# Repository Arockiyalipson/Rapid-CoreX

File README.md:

# Rapid_CoreX 

## Introduction

Rapid-CoreX is a versatile Rapid control prototyping (RCP) designed for embedded systems development, testing, and integration. It supports essential communication protocols and allows for easy connection and testing of various sensors or devices using MATLAB software. Rapid-CoreX is particularly useful for testing external parameters of Battery Management Systems (BMS), motor controllers, and other connected devices.

## Tools Used

- **KiCad:** Used for schematic capture and PCB layout design.
- **STM32CubeMX:** Used for setting up the pin map for the design

## Design Structure

```bash
Rapid-CoreX
        │
        ├───Design
        │
        ├───Images
        │
        ├───Library
        │   ├───Symbols
        │   ├───Footprint
        │   └───3D_Images
        ├───Manufacturing_files
        │   ├───Bom file
        │   ├───Component position files
        │   ├───Drill files
        │   ├───Gerber files
        │   └───Reference_material
        └───Reference
```

## Features

### Communication Protocols

Rapid-CoreX includes the following communication protocols for sensor connection, data collection, and interconnection:

#### Basic Protocols

- **SPI**: Serial Peripheral Interface for high-speed communication.
- **I2C**: Inter-Integrated Circuit for connecting multiple sensors.
- **UART**: Universal Asynchronous Receiver-Transmitter for serial communication.

#### Debugging

- **SWD**: Serial Wire Debug for in-circuit debugging and programming.

#### Data Collection and Interconnection Protocols

- **CAN**: Controller Area Network for real-time data exchange in automotive and industrial applications.
- **RS-485**: A robust standard for long-distance communication.
- **LIN**: Local Interconnect Network, used in automotive networks for communication between components.

All data collection protocols are isolated to ensure better protection and signal integrity.

### Communication Ports

Rapid-CoreX is equipped with various ports to facilitate connectivity:

- **2 x CAN** ports for network communication.
- **2 x RS-485** ports (USART) for long-distance and robust communication.
- **2 x LIN** ports for automotive applications.
- **1 x External SPI** ports for additional SPI device connectivity.

### GPIO Features

- **User LED**: Available for user-defined visual indication.

## Applications

Rapid-CoreX is ideal for:

- Testing external parameters of Battery Management Systems (BMS).
- Testing motor controllers.
- Integrating and testing various sensors.
- Development and testing of embedded systems that require robust and isolated communication.

## Getting Started

### Prerequisites

To use Rapid-CoreX, ensure you have the following:

- MATLAB software for interfacing and testing.
- Necessary drivers and libraries for STM32 Cortex-M4.

### Setup

1. Connect your sensors or sister devices to the appropriate communication ports on Rapid-CoreX.
2. Use MATLAB to interface with Rapid-CoreX for data collection and testing.
3. For debugging, connect through the SWD interface.

### Usage

1. Power on the Rapid-CoreX and ensure all connections are secure.
2. Implement a MATLAB Developed Algorithm in the board
3. Start collecting Data and Analyze it 

## Contact

For more information, please contact [Arockiya Lipson](https://www.linkedin.com/in/arockiya-lipson-458b12214).

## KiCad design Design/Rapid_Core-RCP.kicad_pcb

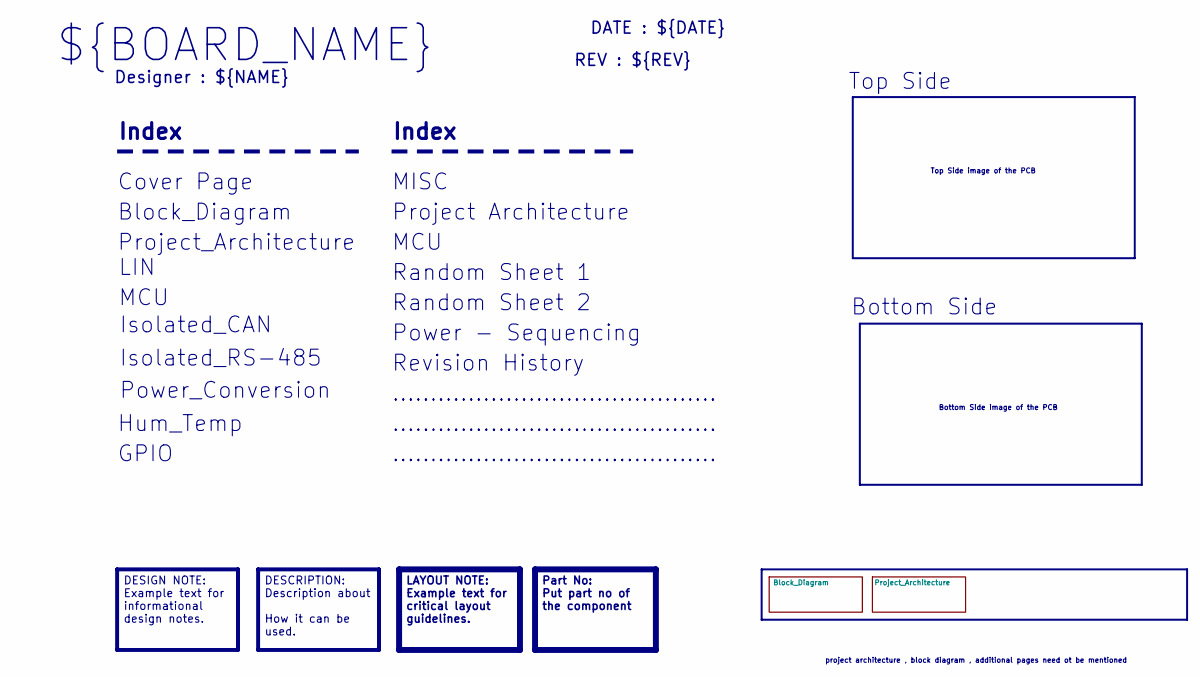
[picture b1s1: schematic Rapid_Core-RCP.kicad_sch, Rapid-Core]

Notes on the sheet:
DESCRIPTION: Description about How it can be used.
Part No: Put part no of the component
DESIGN NOTE: Example text for informational design notes.
LAYOUT NOTE: Example text for critical layout guidelines.
...........................................
Top Side image of the PCB
MISC
Power_Conversion
Designer : ${NAME}
Random Sheet 1
Revision History
Hum_Temp
project architecture , block diagram , additional pages need ot be mentioned
Cover Page
Power - Sequencing
Bottom Side image of the PCB
DATE : ${DATE}
Project_Architecture
Top Side
Isolated_RS-485
${BOARD_NAME}
Index
Bottom Side
REV : ${REV}
GPIO
Isolated_CAN
Random Sheet 2
MCU
Project Architecture
LIN
Block_Diagram

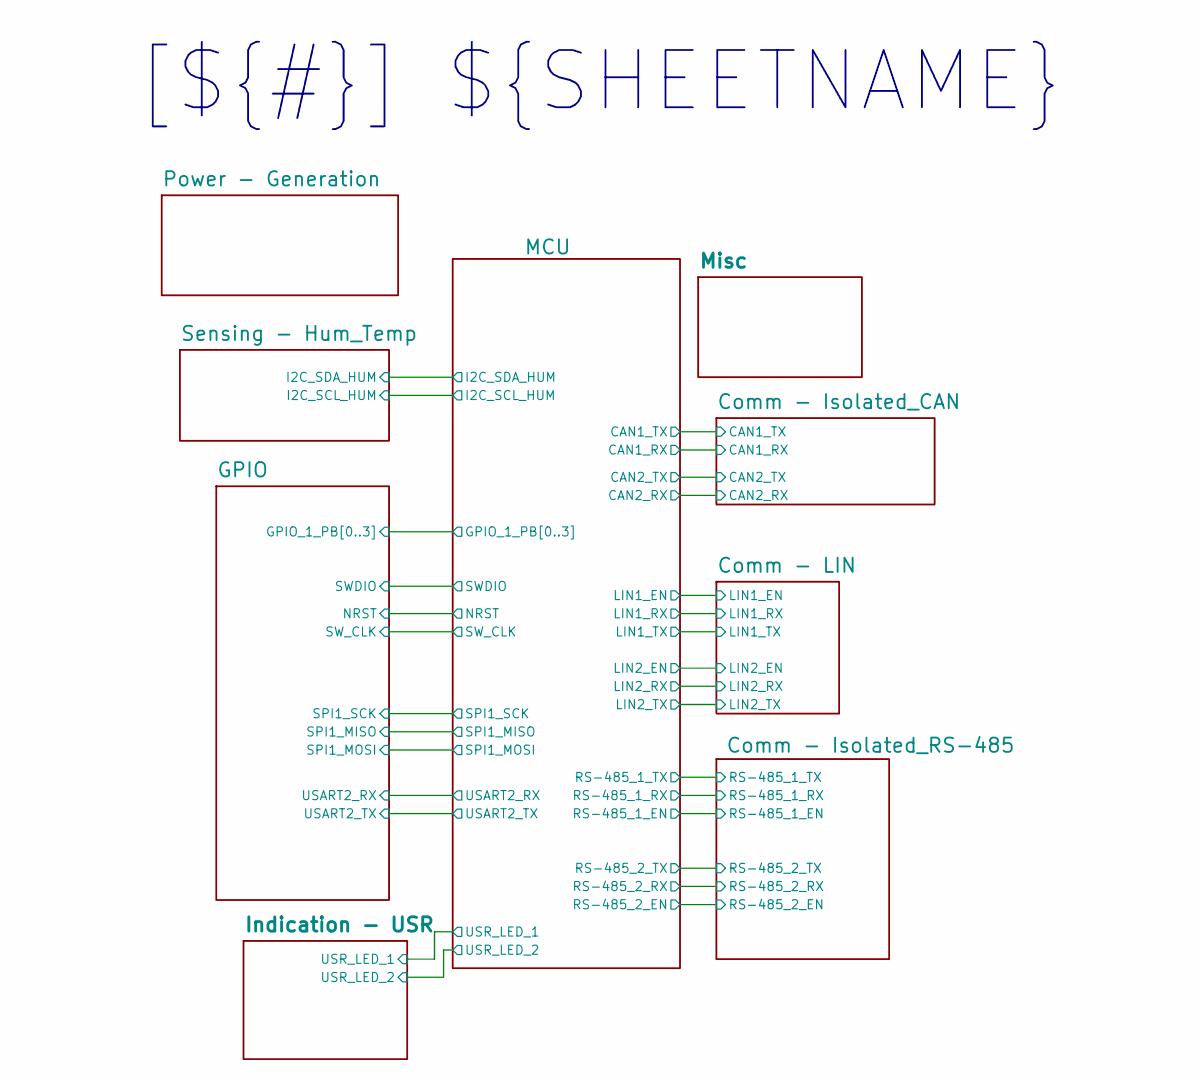
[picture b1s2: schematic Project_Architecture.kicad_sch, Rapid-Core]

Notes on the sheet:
[${#}] ${SHEETNAME}

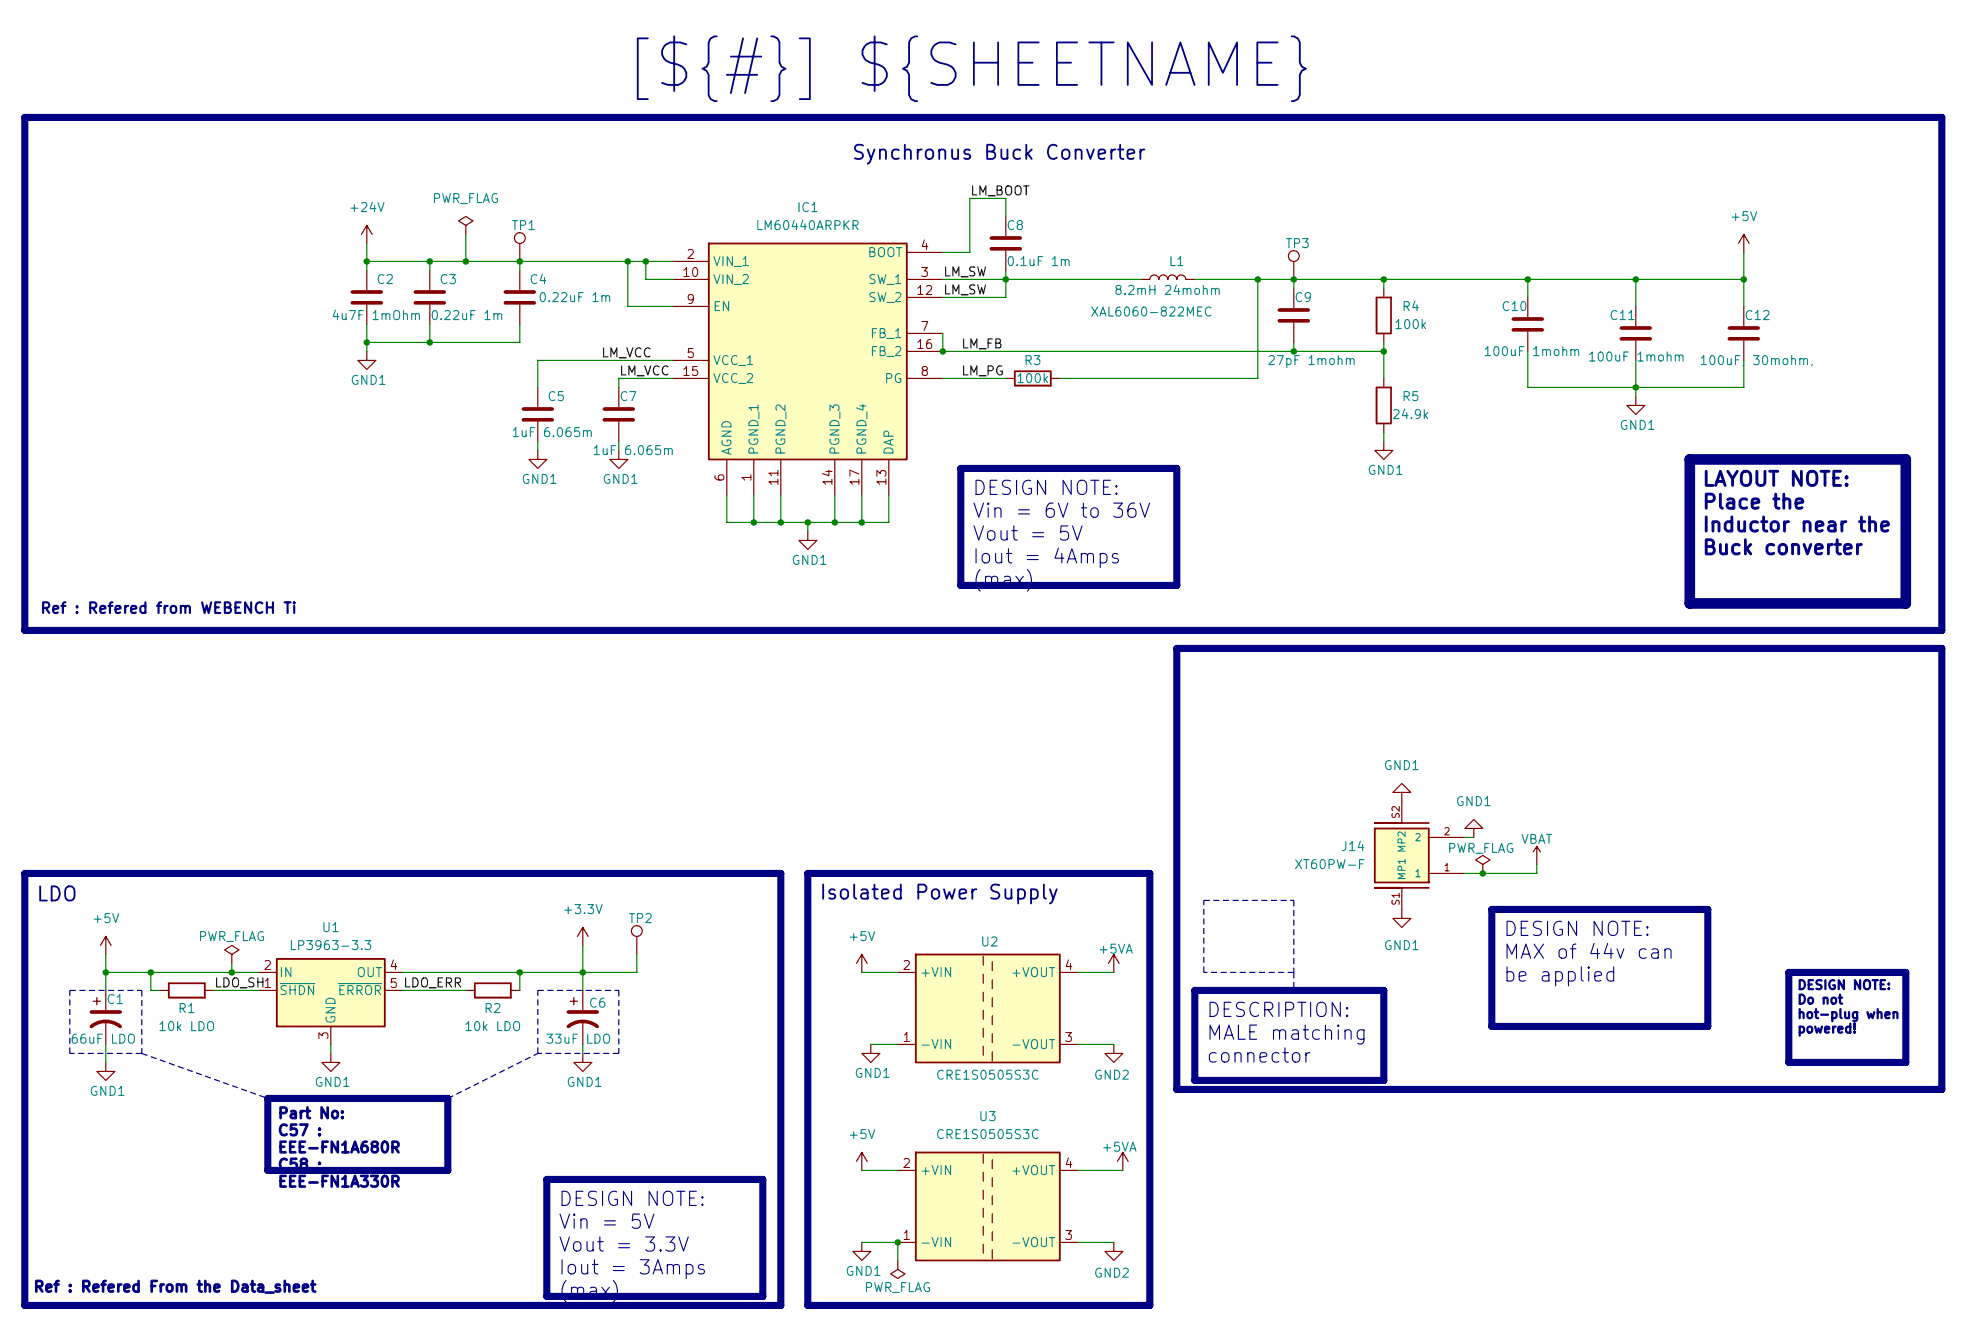
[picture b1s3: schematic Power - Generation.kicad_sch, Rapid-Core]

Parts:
C1: 66uF LDO; CP_Elec_5x5.8
C2: 4u7F 1mOhm; C_0805_2012Metric_Pad1.18x1.45mm_HandSolder
C3, C4: 0.22uF 1m; C_0603_1608Metric_Pad1.08x0.95mm_HandSolder
C5, C7: 1uF 6.065m; C_0603_1608Metric_Pad1.08x0.95mm_HandSolder
C6: 33uF LDO; CP_Elec_4x5.8
C8: 0.1uF 1m; C_0603_1608Metric_Pad1.08x0.95mm_HandSolder
C9: 27pF 1mohm; C_0805_2012Metric_Pad1.18x1.45mm_HandSolder
C10, C11: 100uF 1mohm; C_0805_2012Metric_Pad1.18x1.45mm_HandSolder
C12: 100uF, 30mohm,; C_0805_2012Metric_Pad1.18x1.45mm_HandSolder
IC1: LM60440ARPKR; LM60440AQRPKRQ1; Mouser Part Number 595-LM60440ARPKR
J14: XT60PW-F; AMASS_XT60PW-F
L1: 8.2mH 24mohm; L_Coilcraft_XAL6060-XXX; MANUFACTURER PART NO XAL6060-822MEC
R1, R2: 10k LDO; R_0805_2012Metric_Pad1.20x1.40mm_HandSolder
R3, R4: 100k; R_0805_2012Metric_Pad1.20x1.40mm_HandSolder
R5: 24.9k; R_0805_2012Metric_Pad1.20x1.40mm_HandSolder
TP1, TP2, TP3: TestPoint; TestPoint_Pad_D1.0mm
U1: LP3963-3.3; TO-263-5_TabPin3
U2, U3: CRE1S0505S3C; Converter_DCDC_Murata_CRE1xxxxxx3C_THT

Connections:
+3.3V: C6.1, R2.2, TP2.1, U1.4 (OUT); also elsewhere on the board
+5V: C1.1, C9.1, C10.1, C11.1, C12.1, L1.2, R1.1, R3.2, R4.2, TP3.1, U1.2 (IN), U2.2 (+VIN), U3.2 (+VIN); also elsewhere on the board
+5VA: U2.4 (+VOUT), U3.4 (+VOUT); also elsewhere on the board
+24V: C2.1, C3.1, C4.1, IC1.2 (VIN_1), IC1.9 (EN), IC1.10 (VIN_2), TP1.1
/Project_Architecture/Power - Generation/LDO_ERR: R2.1, U1.5 (~ERROR)
/Project_Architecture/Power - Generation/LDO_SH: R1.2, U1.1 (~SHDN)
/Project_Architecture/Power - Generation/LM_BOOT: C8.1, IC1.4 (BOOT)
/Project_Architecture/Power - Generation/LM_FB: C9.2, IC1.7 (FB_1), IC1.16 (FB_2), R4.1, R5.2
/Project_Architecture/Power - Generation/LM_PG: IC1.8 (PG), R3.1
/Project_Architecture/Power - Generation/LM_SW: C8.2, IC1.3 (SW_1), IC1.12 (SW_2), L1.1
/Project_Architecture/Power - Generation/LM_VCC: C5.1, C7.1, IC1.5 (VCC_1), IC1.15 (VCC_2)
GND1: C1.2, C2.2, C3.2, C4.2, C5.2, C6.2, C7.2, C10.2, C11.2, C12.2, IC1.1 (PGND_1), IC1.6 (AGND), IC1.11 (PGND_2), IC1.13 (DAP), IC1.14 (PGND_3), IC1.17 (PGND_4), J14.2, J14.S1 (MP1), J14.S2 (MP2), R5.1, U1.3 (GND), U2.1 (-VIN), U3.1 (-VIN); also elsewhere on the board
GND2: U2.3 (-VOUT), U3.3 (-VOUT); also elsewhere on the board
VBAT: J14.1

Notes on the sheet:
DESIGN NOTE: Vin = 5V Vout = 3.3V Iout = 3Amps (max)
DESIGN NOTE: Vin = 6V to 36V Vout = 5V Iout = 4Amps (max)
DESIGN NOTE: MAX of 44v can be applied
LAYOUT NOTE: Place the Inductor near the Buck converter
Part No: C57 : EEE-FN1A680R C58 : EEE-FN1A330R
DESCRIPTION: MALE matching connector
DESIGN NOTE: Do not hot-plug when powered!
[${#}] ${SHEETNAME}
Isolated Power Supply
LDO
Ref : Refered From the Data_sheet
Synchronus Buck Converter
Ref : Refered from WEBENCH Ti

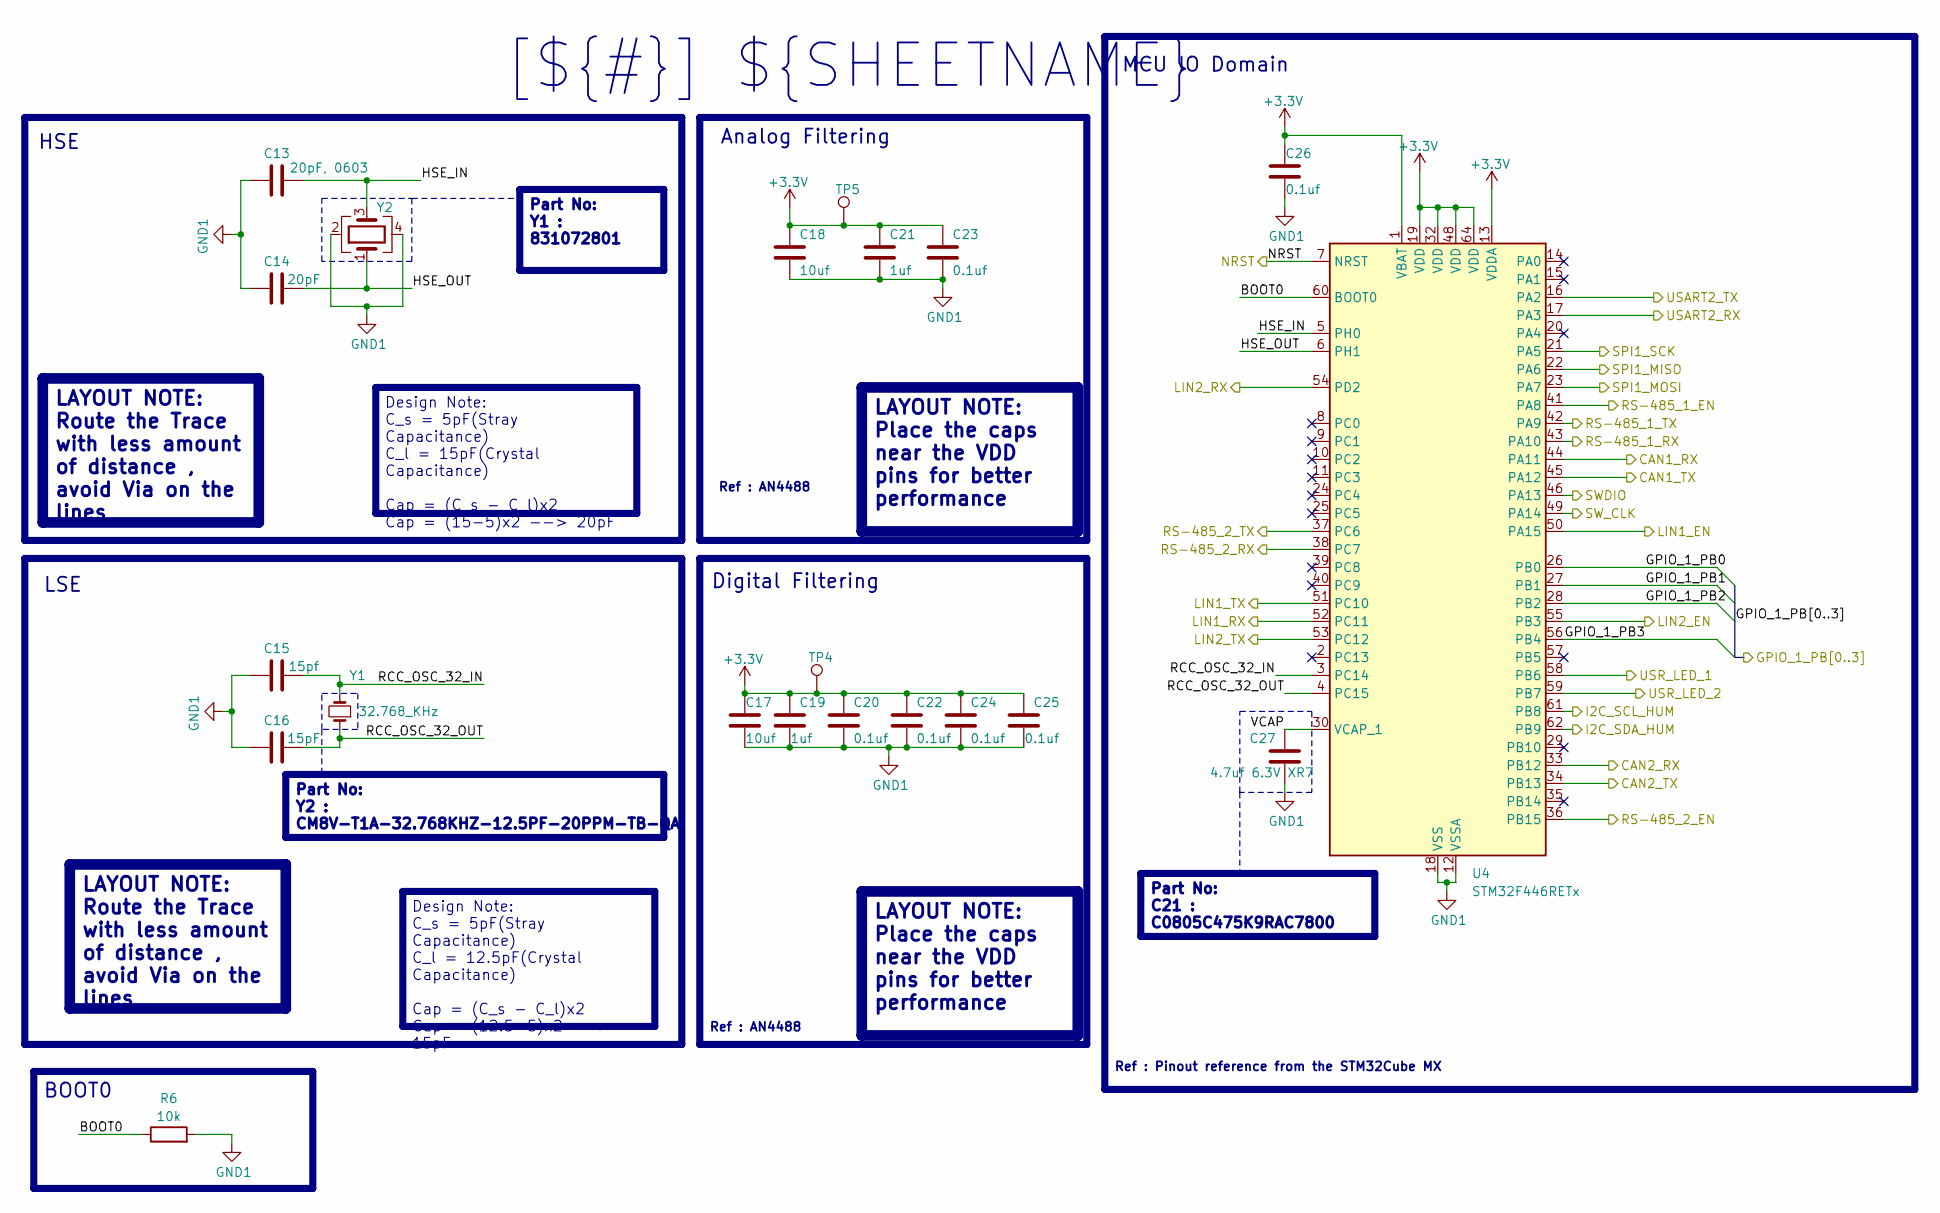
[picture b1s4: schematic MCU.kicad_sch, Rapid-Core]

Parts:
C13: 20pF, 0603; C_0603_1608Metric
C14: 20pF; C_0603_1608Metric
C15: 15pf; C_0603_1608Metric
C16: 15pF; C_0603_1608Metric
C17, C18: 10uf; C_0805_2012Metric_Pad1.18x1.45mm_HandSolder
C19, C21: 1uf; C_0603_1608Metric_Pad1.08x0.95mm_HandSolder
C20, C22, C23, C24, C25, C26: 0.1uf; C_0603_1608Metric_Pad1.08x0.95mm_HandSolder
C27: 4.7uf 6.3V XR7; C_0805_2012Metric_Pad1.18x1.45mm_HandSolder
R6: 10k; R_0805_2012Metric_Pad1.20x1.40mm_HandSolder
TP4, TP5: TestPoint; TestPoint_Pad_D1.0mm
U4: STM32F446RETx; LQFP-64_10x10mm_P0.5mm
Y1: 32.768_KHz; Crystal_SMD_MicroCrystal_CC8V-T1A-2Pin_2.0x1.2mm
Y2: Crystal_GND24; Crystal_SMD_2520-4Pin_2.5x2.0mm

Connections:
+3.3V: C17.1, C18.1, C19.1, C20.1, C21.1, C22.1, C23.1, C24.1, C25.1, C26.1, TP4.1, TP5.1, U4.1 (VBAT), U4.13 (VDDA), U4.19 (VDD), U4.32 (VDD), U4.48 (VDD), U4.64 (VDD); also elsewhere on the board
/Project_Architecture/Comm - Isolated_CAN/CAN1_RX: U4.44 (PA11); also elsewhere on the board
/Project_Architecture/Comm - Isolated_CAN/CAN1_TX: U4.45 (PA12); also elsewhere on the board
/Project_Architecture/Comm - Isolated_CAN/CAN2_RX: U4.33 (PB12); also elsewhere on the board
/Project_Architecture/Comm - Isolated_CAN/CAN2_TX: U4.34 (PB13); also elsewhere on the board
/Project_Architecture/Comm - Isolated_RS-485/RS-485_1_EN: U4.41 (PA8); also elsewhere on the board
/Project_Architecture/Comm - Isolated_RS-485/RS-485_1_RX: U4.43 (PA10); also elsewhere on the board
/Project_Architecture/Comm - Isolated_RS-485/RS-485_1_TX: U4.42 (PA9); also elsewhere on the board
/Project_Architecture/Comm - Isolated_RS-485/RS-485_2_EN: U4.36 (PB15); also elsewhere on the board
/Project_Architecture/Comm - Isolated_RS-485/RS-485_2_RX: U4.38 (PC7); also elsewhere on the board
/Project_Architecture/Comm - Isolated_RS-485/RS-485_2_TX: U4.37 (PC6); also elsewhere on the board
/Project_Architecture/Comm - LIN/LIN1_EN: U4.50 (PA15); also elsewhere on the board
/Project_Architecture/Comm - LIN/LIN1_RX: U4.52 (PC11); also elsewhere on the board
/Project_Architecture/Comm - LIN/LIN1_TX: U4.51 (PC10); also elsewhere on the board
/Project_Architecture/Comm - LIN/LIN2_EN: U4.55 (PB3); also elsewhere on the board
/Project_Architecture/Comm - LIN/LIN2_RX: U4.54 (PD2); also elsewhere on the board
/Project_Architecture/Comm - LIN/LIN2_TX: U4.53 (PC12); also elsewhere on the board
/Project_Architecture/GPIO/GPIO_1_PB0: U4.26 (PB0); also elsewhere on the board
/Project_Architecture/GPIO/GPIO_1_PB1: U4.27 (PB1); also elsewhere on the board
/Project_Architecture/GPIO/GPIO_1_PB2: U4.28 (PB2); also elsewhere on the board
/Project_Architecture/GPIO/GPIO_1_PB3: U4.56 (PB4); also elsewhere on the board
/Project_Architecture/GPIO/NRST: U4.7 (NRST); also elsewhere on the board
/Project_Architecture/GPIO/SPI1_MISO: U4.22 (PA6); also elsewhere on the board
/Project_Architecture/GPIO/SPI1_MOSI: U4.23 (PA7); also elsewhere on the board
/Project_Architecture/GPIO/SPI1_SCK: U4.21 (PA5); also elsewhere on the board
/Project_Architecture/GPIO/SWDIO: U4.46 (PA13); also elsewhere on the board
/Project_Architecture/GPIO/SW_CLK: U4.49 (PA14); also elsewhere on the board
/Project_Architecture/GPIO/USART2_RX: U4.17 (PA3); also elsewhere on the board
/Project_Architecture/GPIO/USART2_TX: U4.16 (PA2); also elsewhere on the board
/Project_Architecture/Indication - USR/USR_LED_1: U4.58 (PB6); also elsewhere on the board
/Project_Architecture/Indication - USR/USR_LED_2: U4.59 (PB7); also elsewhere on the board
/Project_Architecture/MCU/BOOT0: R6.1, U4.60 (BOOT0)
/Project_Architecture/MCU/HSE_IN: C13.2, U4.5 (PH0), Y2.3
/Project_Architecture/MCU/HSE_OUT: C14.2, U4.6 (PH1), Y2.1
/Project_Architecture/MCU/I2C_SCL_HUM: U4.61 (PB8); also elsewhere on the board
/Project_Architecture/MCU/I2C_SDA_HUM: U4.62 (PB9); also elsewhere on the board
/Project_Architecture/MCU/RCC_OSC_32_IN: C15.2, U4.3 (PC14), Y1.2
/Project_Architecture/MCU/RCC_OSC_32_OUT: C16.2, U4.4 (PC15), Y1.1
/Project_Architecture/MCU/VCAP: C27.1, U4.30 (VCAP_1)
GND1: C13.1, C14.1, C15.1, C16.1, C17.2, C18.2, C19.2, C20.2, C21.2, C22.2, C23.2, C24.2, C25.2, C26.2, C27.2, R6.2, U4.12 (VSSA), U4.18 (VSS), U4.31 (VSS), U4.47 (VSS), U4.63 (VSS), Y2.2, Y2.4; also elsewhere on the board

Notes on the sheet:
Design Note: C_s = 5pF(Stray Capacitance) C_l = 12.5pF(Crystal Capacitance) Cap = (C_s - C_l)x2 Cap = (12.5-5)x2 --> 15pF
Design Note: C_s = 5pF(Stray Capacitance) C_l = 15pF(Crystal Capacitance) Cap = (C_s - C_l)x2 Cap = (15-5)x2 --> 20pF
Part No: C21 : C0805C475K9RAC7800
Part No: Y2 : CM8V-T1A-32.768KHZ-12.5PF-20PPM-TB-QA
LAYOUT NOTE: Route the Trace with less amount of distance , avoid Via on the lines
LAYOUT NOTE: Place the caps near the VDD pins for better performance
Part No: Y1 : 831072801
Ref : AN4488
[${#}] ${SHEETNAME}
Digital Filtering
Analog Filtering
Ref : Pinout reference from the STM32Cube MX
BOOT0
LSE
MCU IO Domain
HSE

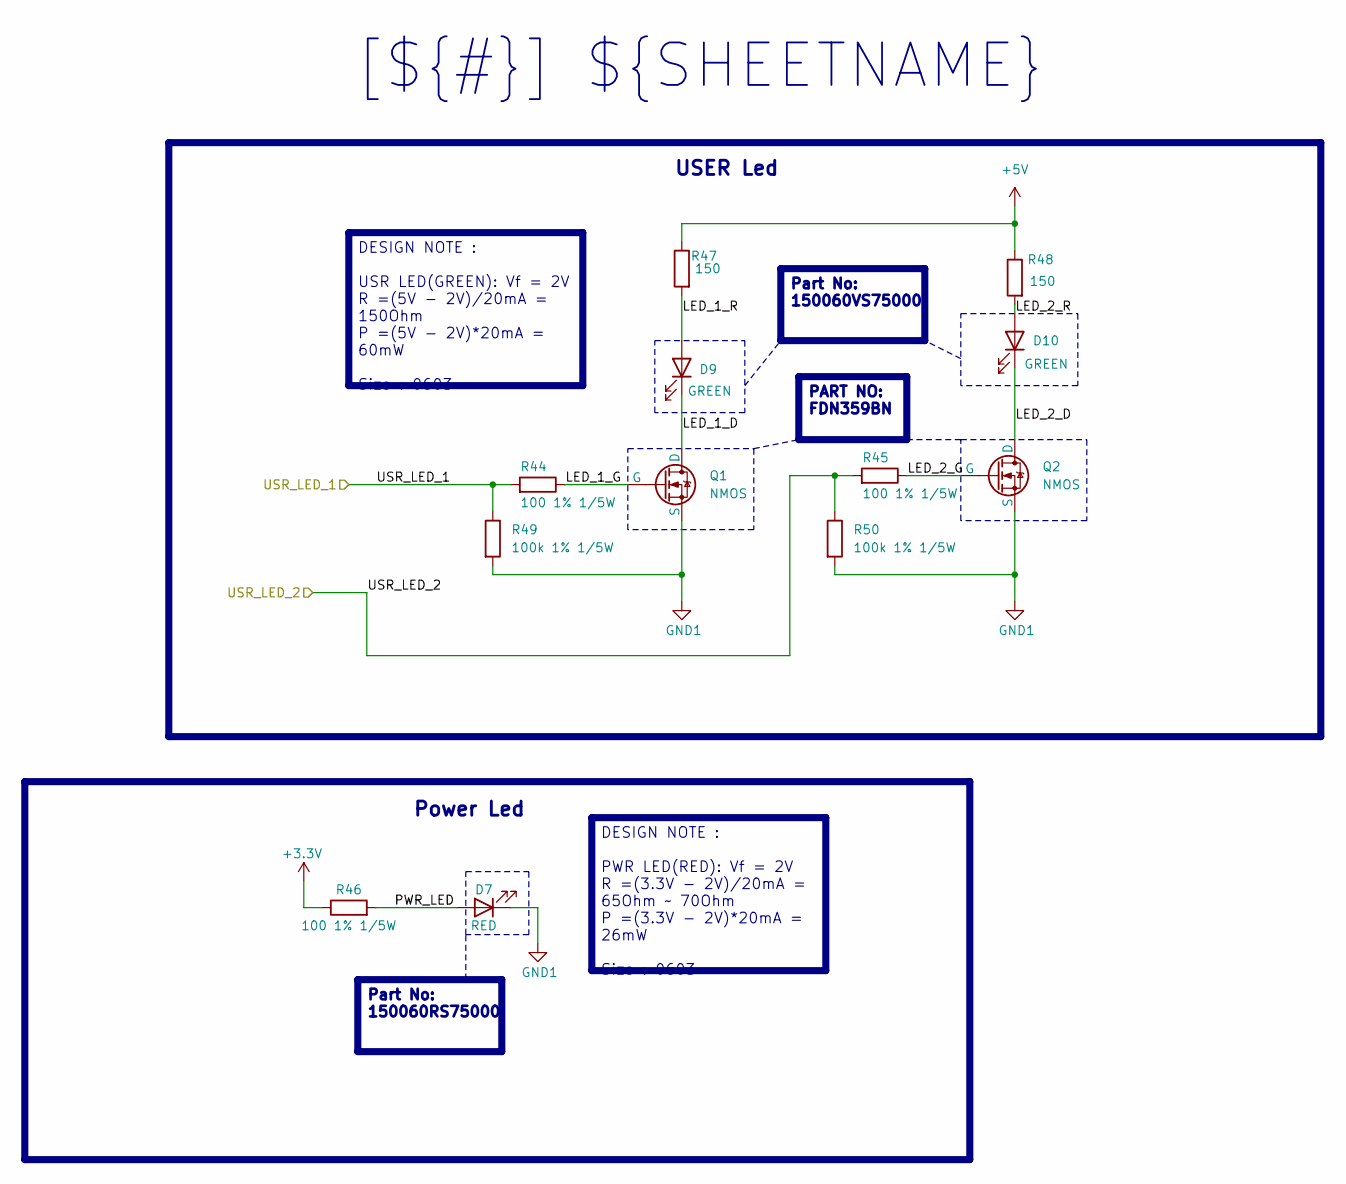
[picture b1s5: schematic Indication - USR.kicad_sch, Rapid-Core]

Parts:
D7: RED; LED_0603_1608Metric_Pad1.05x0.95mm_HandSolder
D9, D10: GREEN; LED_0603_1608Metric_Pad1.05x0.95mm_HandSolder
Q1, Q2: NMOS; SuperSOT-3
R44, R45, R46: 100 1% 1/5W; R_0603_1608Metric_Pad0.98x0.95mm_HandSolder
R47, R48: 150; R_0603_1608Metric_Pad0.98x0.95mm_HandSolder
R49, R50: 100k 1% 1/5W; R_0603_1608Metric_Pad0.98x0.95mm_HandSolder

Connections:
+3.3V: R46.1; also elsewhere on the board
+5V: R47.1, R48.1; also elsewhere on the board
/Project_Architecture/Indication - USR/LED_1_D: D9.1 (K), Q1.1 (D)
/Project_Architecture/Indication - USR/LED_1_G: Q1.2 (G), R44.1
/Project_Architecture/Indication - USR/LED_1_R: D9.2 (A), R47.2
/Project_Architecture/Indication - USR/LED_2_D: D10.1 (K), Q2.1 (D)
/Project_Architecture/Indication - USR/LED_2_G: Q2.2 (G), R45.1
/Project_Architecture/Indication - USR/LED_2_R: D10.2 (A), R48.2
/Project_Architecture/Indication - USR/PWR_LED: D7.2 (A), R46.2
/Project_Architecture/Indication - USR/USR_LED_1: R44.2, R49.1; also elsewhere on the board
/Project_Architecture/Indication - USR/USR_LED_2: R45.2, R50.1; also elsewhere on the board
GND1: D7.1 (K), Q1.3 (S), Q2.3 (S), R49.2, R50.2; also elsewhere on the board

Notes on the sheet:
DESIGN NOTE : PWR LED(RED): Vf = 2V R =(3.3V - 2V)/20mA = 65Ohm ~ 70Ohm P =(3.3V - 2V)*20mA = 26mW Size : 0603
PART NO: FDN359BN
Part No: 150060VS75000
Part No: 150060RS75000
DESIGN NOTE : USR LED(GREEN): Vf = 2V R =(5V - 2V)/20mA = 150Ohm P =(5V - 2V)*20mA = 60mW Size : 0603
[${#}] ${SHEETNAME}
USER Led
Power Led

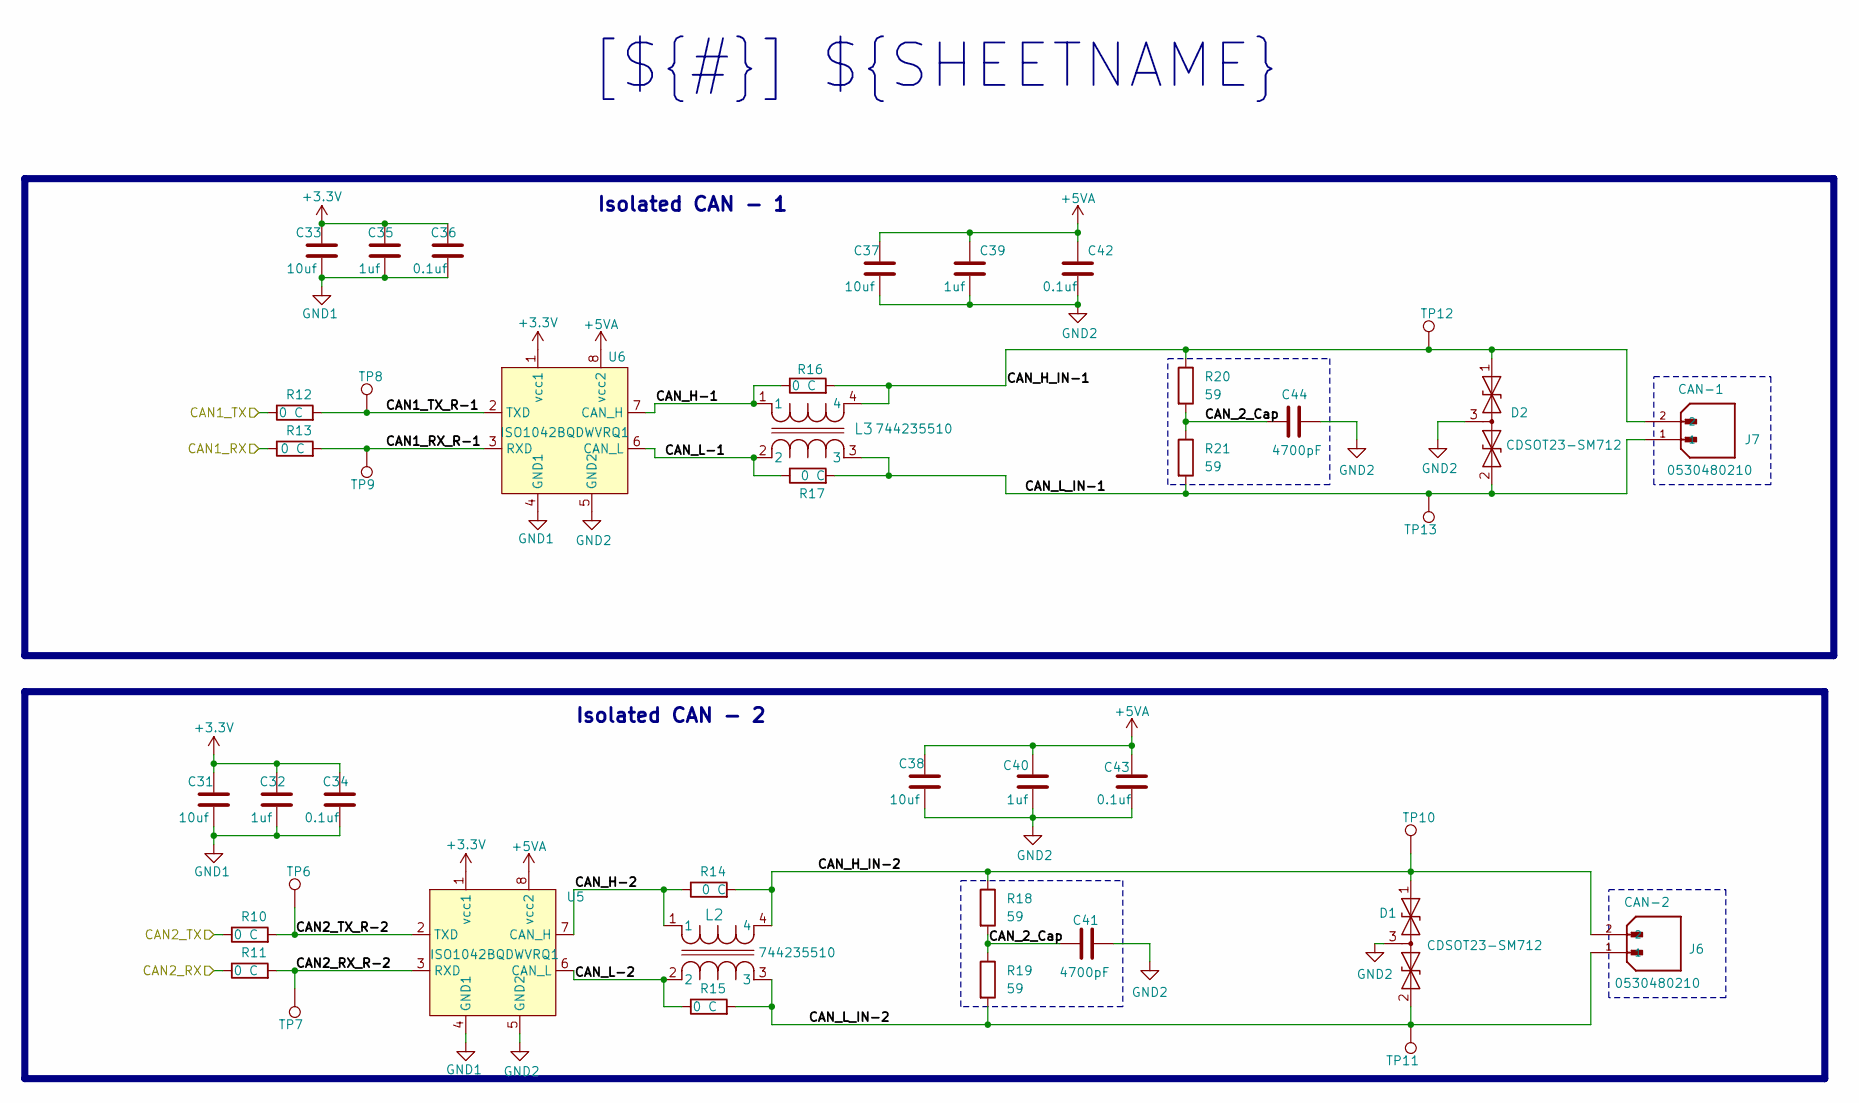
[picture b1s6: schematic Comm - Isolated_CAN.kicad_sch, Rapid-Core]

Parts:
C31, C33, C37, C38: 10uf; C_0805_2012Metric_Pad1.18x1.45mm_HandSolder
C32, C35, C39, C40: 1uf; C_0603_1608Metric_Pad1.08x0.95mm_HandSolder
C34, C36, C42, C43: 0.1uf; C_0603_1608Metric_Pad1.08x0.95mm_HandSolder
C41, C44: 4700pF; C_0805_2012Metric_Pad1.18x1.45mm_HandSolder
D1: SM712_SOT23; SOT-23; MANUFACTURER PART NO CDSOT23-SM712
D2: SM712_SOT23; SOT-23; Manufacturer Part No CDSOT23-SM712
J6: CAN-2; MOLEX_530480210; PARTREV A
J7: CAN-1; MOLEX_530480210; PARTREV A
L2, L3: ACT45B-510-2P-TL003; IND_ACT45R_TDK; MANUFACTURER PART NO 744235510
R10, R11, R12, R13, R14, R15, R16, R17: 0 C; R_0805_2012Metric_Pad1.20x1.40mm_HandSolder
R18, R19, R20, R21: 59; R_0603_1608Metric_Pad0.98x0.95mm_HandSolder
TP6, TP7, TP8, TP9, TP10, TP11, TP12, TP13: TestPoint; TestPoint_Pad_D1.0mm
U5, U6: ISO1042BQDWVRQ1; IC_AMC1311BQDWVQ1

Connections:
+3.3V: C31.1, C32.1, C33.1, C34.2, C35.1, C36.2, U5.1 (vcc1), U6.1 (vcc1); also elsewhere on the board
+5VA: C37.1, C38.1, C39.1, C40.1, C42.2, C43.2, U5.8 (vcc2), U6.8 (vcc2); also elsewhere on the board
/Project_Architecture/Comm - Isolated_CAN/CAN1_RX: R13.1; also elsewhere on the board
/Project_Architecture/Comm - Isolated_CAN/CAN1_RX_R-1: R13.2, TP9.1, U6.3 (RXD)
/Project_Architecture/Comm - Isolated_CAN/CAN1_TX: R12.1; also elsewhere on the board
/Project_Architecture/Comm - Isolated_CAN/CAN1_TX_R-1: R12.2, TP8.1, U6.2 (TXD)
/Project_Architecture/Comm - Isolated_CAN/CAN2_RX: R11.1; also elsewhere on the board
/Project_Architecture/Comm - Isolated_CAN/CAN2_RX_R-2: R11.2, TP7.1, U5.3 (RXD)
/Project_Architecture/Comm - Isolated_CAN/CAN2_TX: R10.1; also elsewhere on the board
/Project_Architecture/Comm - Isolated_CAN/CAN2_TX_R-2: R10.2, TP6.1, U5.2 (TXD)
/Project_Architecture/Comm - Isolated_CAN/CAN_2_Cap: C41.1, C44.1, R18.2, R19.1, R20.2, R21.1
/Project_Architecture/Comm - Isolated_CAN/CAN_H-1: L3.1, R16.1, U6.7 (CAN_H)
/Project_Architecture/Comm - Isolated_CAN/CAN_H-2: L2.1, R14.1, U5.7 (CAN_H)
/Project_Architecture/Comm - Isolated_CAN/CAN_H_IN-1: D2.1 (A1), J7.2, L3.4, R16.2, R20.1, TP12.1
/Project_Architecture/Comm - Isolated_CAN/CAN_H_IN-2: D1.1 (A1), J6.2, L2.4, R14.2, R18.1, TP10.1
/Project_Architecture/Comm - Isolated_CAN/CAN_L-1: L3.2, R17.1, U6.6 (CAN_L)
/Project_Architecture/Comm - Isolated_CAN/CAN_L-2: L2.2, R15.1, U5.6 (CAN_L)
/Project_Architecture/Comm - Isolated_CAN/CAN_L_IN-1: D2.2 (A2), J7.1, L3.3, R17.2, R21.2, TP13.1
/Project_Architecture/Comm - Isolated_CAN/CAN_L_IN-2: D1.2 (A2), J6.1, L2.3, R15.2, R19.2, TP11.1
GND1: C31.2, C32.2, C33.2, C34.1, C35.2, C36.1, U5.4 (GND1), U6.4 (GND1); also elsewhere on the board
GND2: C37.2, C38.2, C39.2, C40.2, C41.2, C42.1, C43.1, C44.2, D1.3 (common), D2.3 (common), U5.5 (GND2), U6.5 (GND2); also elsewhere on the board

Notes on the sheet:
Isolated CAN - 1
Isolated CAN - 2
[${#}] ${SHEETNAME}

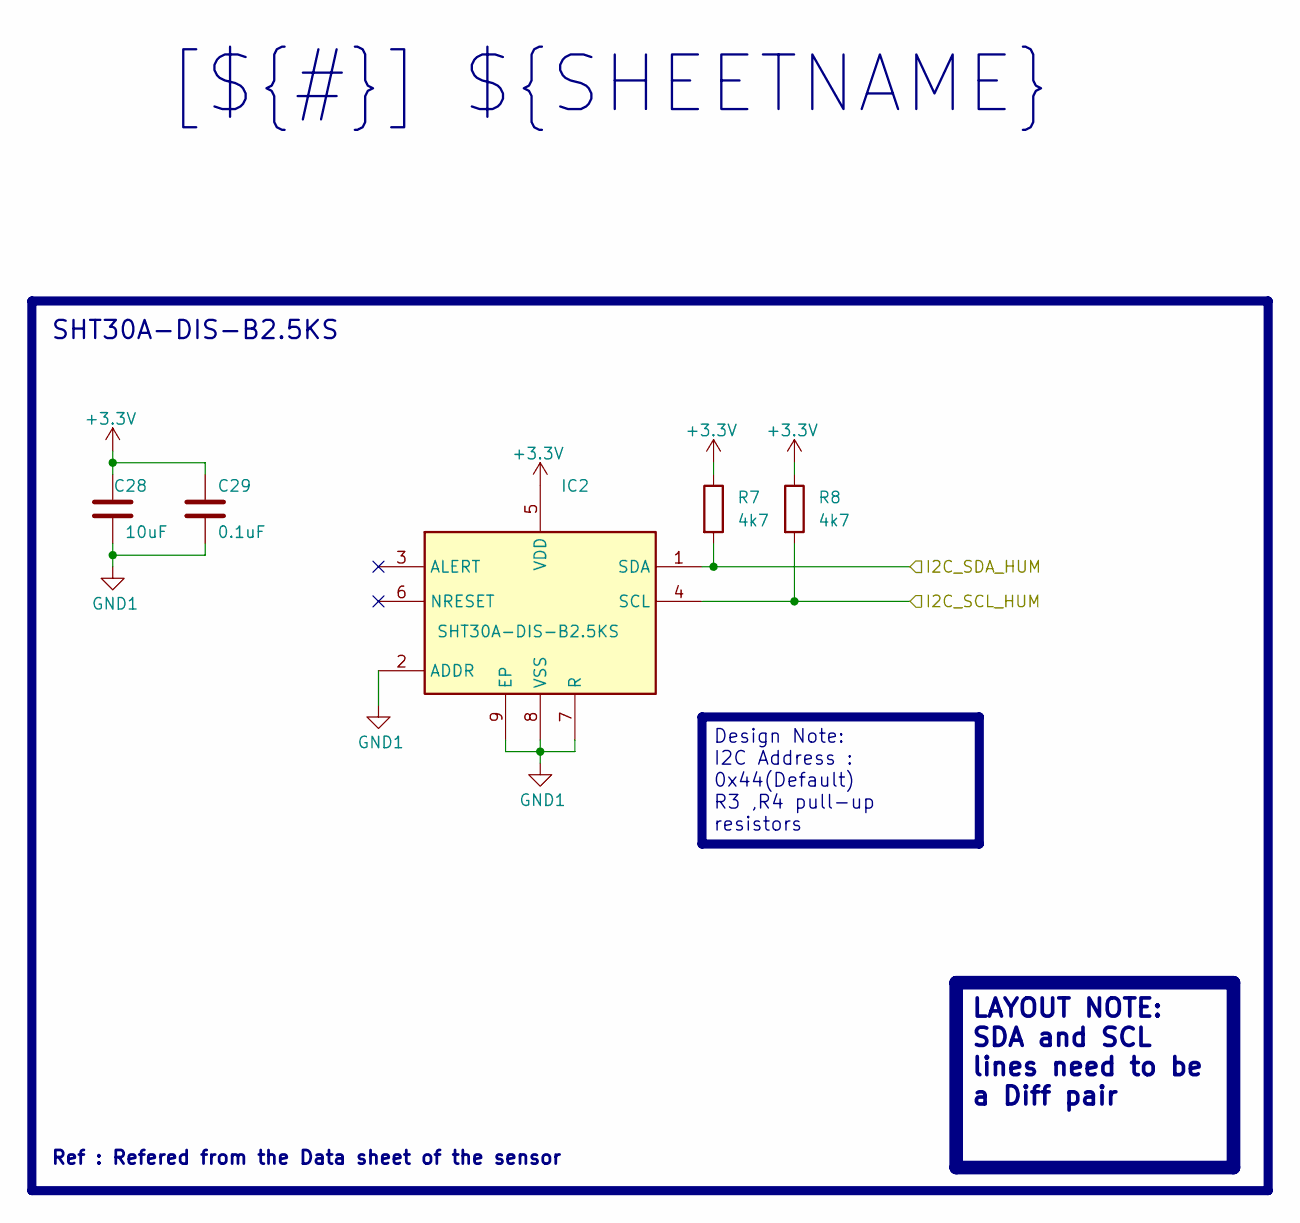
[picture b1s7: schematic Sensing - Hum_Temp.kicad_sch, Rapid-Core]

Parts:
C28: 10uF; C_0805_2012Metric_Pad1.18x1.45mm_HandSolder
C29: 0.1uF; C_0603_1608Metric_Pad1.08x0.95mm_HandSolder
IC2: SHT30A-DIS-B2.5KS; SON50P250X250X100-9N-D; Mouser Part Number 403-SHT30ADIS-B2.5KS
R7, R8: 4k7; R_0805_2012Metric_Pad1.20x1.40mm_HandSolder

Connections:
+3.3V: C28.1, C29.1, IC2.5 (VDD), R7.1, R8.1; also elsewhere on the board
/Project_Architecture/MCU/I2C_SCL_HUM: IC2.4 (SCL), R8.2; also elsewhere on the board
/Project_Architecture/MCU/I2C_SDA_HUM: IC2.1 (SDA), R7.2; also elsewhere on the board
GND1: C28.2, C29.2, IC2.2 (ADDR), IC2.7 (R), IC2.8 (VSS), IC2.9 (EP); also elsewhere on the board

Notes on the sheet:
Design Note: I2C Address : 0x44(Default) R3 ,R4 pull-up resistors
LAYOUT NOTE: SDA and SCL lines need to be a Diff pair
[${#}] ${SHEETNAME}
Ref : Refered from the Data sheet of the sensor
SHT30A-DIS-B2.5KS

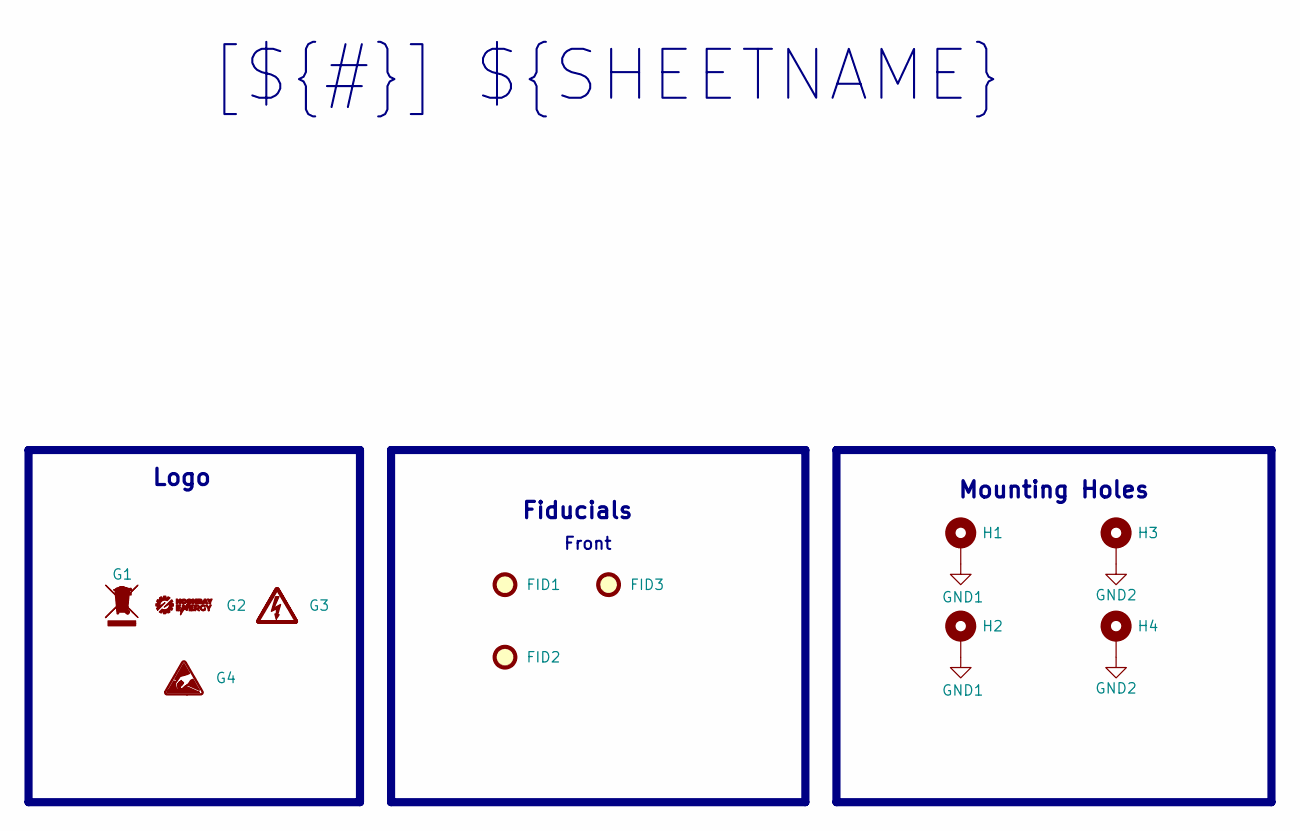
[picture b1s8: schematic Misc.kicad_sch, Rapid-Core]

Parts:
FID1, FID2, FID3: Fiducial; Fiducial_1.5mm_Mask3mm
G1: Not_to_bin; Not_To_Bin
G2: NOON_REAY_ENERGIES; Noon_Ray
G3: High_Voltage_Warning
G4: ESD_Protection; ESD_Protection_Sign
H1, H2, H3, H4: MountingHole_Pad; MountingHole_2.2mm_M2_Pad

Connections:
GND1: H1.1, H2.1; also elsewhere on the board
GND2: H3.1, H4.1; also elsewhere on the board

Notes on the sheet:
Front
[${#}] ${SHEETNAME}
Mounting Holes
Logo
Fiducials

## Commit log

2024-09-11 Added All files
2024-09-11 Added new lines to makdown file
2024-09-12 removed the image
2024-09-12 Added Comps in Communication.sch
2024-09-12 Added reference file for chokless CAN and DC-DC converter in main sch
2024-09-13 Communication.sch modified , 75% finished
2024-09-13 README.md file edited added all neccessary information to it
2024-09-14 Added HUM and TEMP sense
2024-09-14 added new file
2024-09-16 LIN,I2C,SPI,SWD added , Power_stage created
2024-09-17 Setup Power supply
2024-09-18 Footprints added to all componenets
2024-09-18 Added Reference.ioc File
2024-09-18 CMC component name added
2024-09-19 Schematic Design complete
2024-09-24 PCB design started, comps arranged
2024-09-26 Temp complete of communication section , added Safety caps
2024-09-27 value changed for I2C pullup
2024-10-04 Added all the sections
2024-10-06 Added new folder for named Library
2024-10-08 Added lib folder, Layer layed
2024-10-14 End of version 1.0.0 design
2024-10-30 Added everything
2024-11-03 Edited Readme.md file
2024-11-09 Added Information to all the sheets
2024-11-23 Layout complete
2024-11-25 Project finished , man files generated
2024-11-25 updated project status in readme file
2025-03-07 new Design for Prototyping

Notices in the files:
README.md:
License: MIT
